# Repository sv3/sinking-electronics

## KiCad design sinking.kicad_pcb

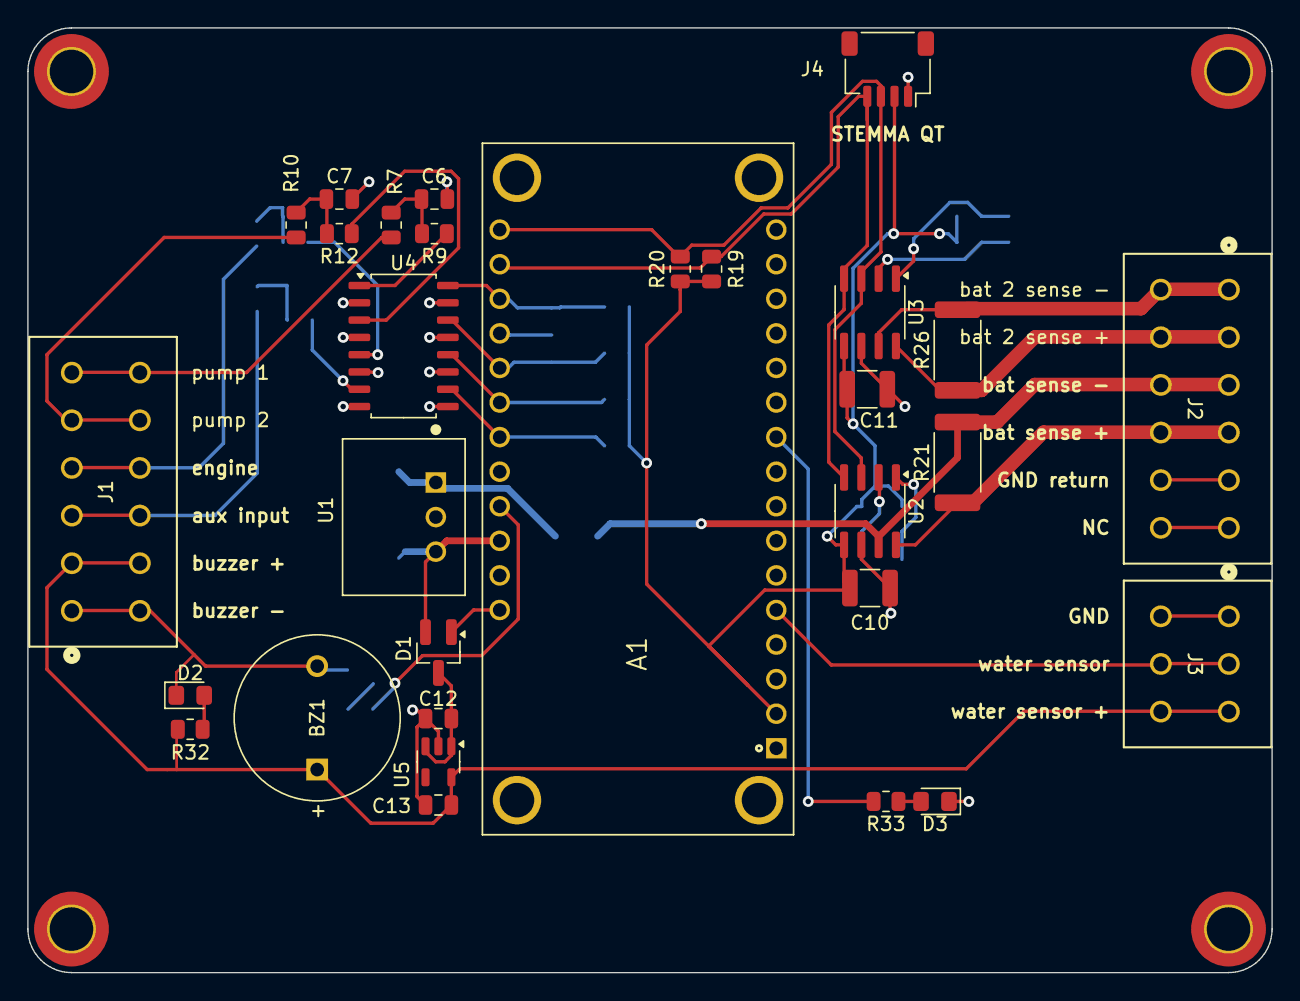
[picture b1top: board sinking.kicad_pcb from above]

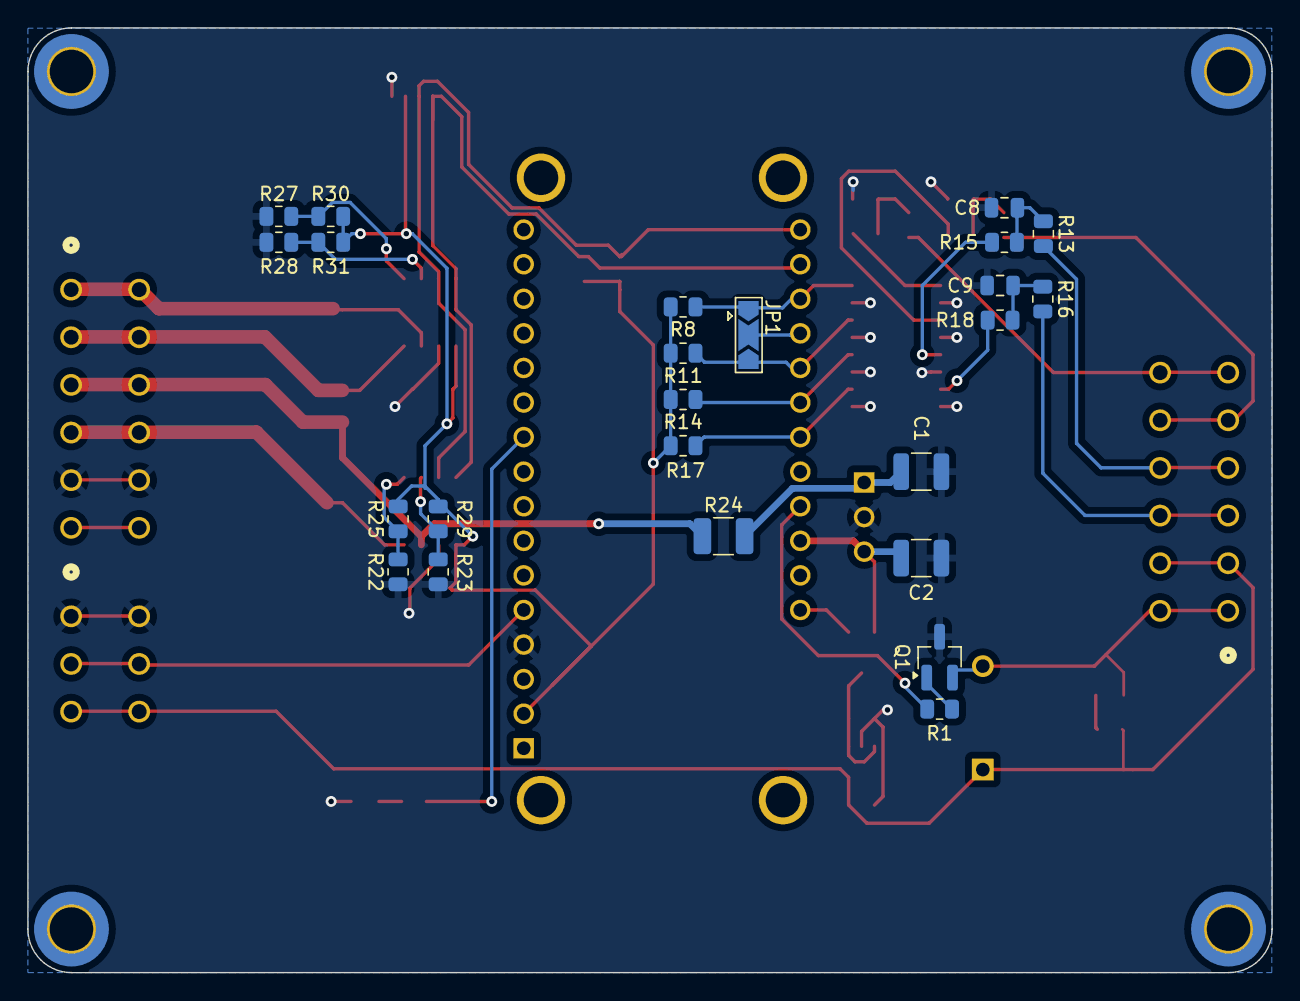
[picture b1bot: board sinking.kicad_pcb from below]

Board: 2 copper layers, 91.4 x 69.4 mm, 54 parts (24 on the bottom side), 42 nets.

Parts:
A1: Particle_Boron; Boron
BZ1: Buzzer; MagneticBuzzer_ProSignal_ABI-009-RC
C1: 10u; C_1210_3225Metric
C2: 22u; C_1210_3225Metric
C6, C7, C8, C9: 4.7u; C_0805_2012Metric
C10, C11: 0.1u; C_1210_3225Metric
C12, C13: 1u; C_0805_2012Metric
D1: PMEG2005; SOT-23_Handsoldering
D2: CTL0805FRD1T; LED_0805_2012Metric_Pad1.15x1.40mm_HandSolder
D3: LED; LED_0805_2012Metric_Pad1.15x1.40mm_HandSolder
J1, J2: 1861975; CONN_1861975
J3: 1861946; CONN_1861946
J4: SM04B-SRSS-TB; JST_SH_SM04B-SRSS-TB_1x04-1MP_P1.00mm_Horizontal
JP1: SolderJumper_3_Open; SolderJumper-3_P2.0mm_Open_TrianglePad1.0x1.5mm
Q1: Q_NPN_BCE; SOT-23_Handsoldering
R1: 1k; R_0805_2012Metric
R7, R9, R10, R12, R13, R15, R16, R18: 2.2k; R_0805_2012Metric
R8, R11, R14, R17: 4.7k; R_0805_2012Metric
R19, R20, R22, R23, R25, R27, R28, R29, R30, R31: 10k; R_0805_2012Metric
R21, R26: 0.1; R_2512_6332Metric
R24: 0; R_1210_3225Metric_Pad1.30x2.65mm_HandSolder
R32, R33: 330; R_0805_2012Metric
U1: V7805-1000; CONV_V7805-1000
U2, U3: INA219AxD; SOIC-8_3.9x4.9mm_P1.27mm
U4: TLP291-4; SOIC-16_4.55x10.3mm_P1.27mm
U5: TPS7A2033PDBVR; SOT-23-5

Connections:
+3V3: A1.3V3, C10.1, C11.1, J4.2, R8.2, R11.2, R14.2, R17.2, R19.2, R20.2, R25.2, R29.2, R30.2, R31.2, U2.5 (VS), U3.5 (VS)
/VUSB: A1.VUSB (VBUS), C2.1, D1.2, U1.3 (+VO)
/Vin: C1.1, R24.2, U1.1 (+VIN)
/input_filter1/out: A1.D4 (UART2_TX_SPI1_MISO_PWM1_P1.08_4), JP1.3 (B), R11.1, U4.14
/input_filter2/out: A1.D5 (UART2_RX_PWM1_P1.10_5), R14.1, U4.12
/input_filter3/out: A1.D6 (UART2_CTS_PWM1_P1.11_6), R17.1, U4.10
/input_filter/out: A1.D2 (SDA1_UART1_RTS_SPI1_SCK_PWM3_P1.01_2), JP1.1 (A), R8.1, U4.16
GND: A1.GND, C1.2, C2.2, C6.2, C7.2, C8.2, C9.2, C10.2, C11.2, C12.2, C13.2, D3.1 (K), J2.9, J2.10, J3.1, J3.2, J4.1, Q1.3 (E), R22.1, R23.1, R27.1, R28.1, U1.2 (GND), U2.6 (GND), U3.6 (GND), U4.2, U4.4, U4.6, U4.8, U4.9, U4.11, U4.13, U4.15, U5.2 (GND)
unnamed: A1.A5 (14_P0.31_PWM3_ADC5_SPI_SS), R33.2
unnamed: A1.LI+ (LiPo+), D1.1
unnamed: A1.D3 (SCL1_UART1_CTS_SPI1_MOSI_PWM3_P1.02_3), JP1.2 (C)
unnamed: A1.D8 (UART2_RTS_PWM1_P1.03_8), R1.1
unnamed: C6.1, R7.1, R9.2
unnamed: C7.1, R10.1, R12.2
unnamed: C8.1, R13.1, R15.2
unnamed: C9.1, R16.1, R18.2
unnamed: D2.2 (A), R32.2
unnamed: D3.2 (A), R33.1
unnamed: J2.11, J2.12
unnamed: Q1.1 (B), R1.2
unnamed: R9.1, U4.1
unnamed: R12.1, U4.3
unnamed: R15.1, U4.5
unnamed: R18.1, U4.7
unnamed: R23.2, R29.1, U2.2 (A0)
unnamed: R22.2, R25.1, U2.1 (A1)
unnamed: R28.2, R31.1, U3.2 (A0)
unnamed: R27.2, R30.1, U3.1 (A1)
unnamed: C12.1, D1.3, U5.1 (IN), U5.3 (EN)
SCL: A1.SCL (1_SCL_P0.27), J4.4, R19.1, U2.4 (SCL), U3.4 (SCL)
SDA: A1.SDA (0_SDA_P0.26), J4.3, R20.1, U2.3 (SDA), U3.3 (SDA)
aux_bat_sense_+: J2.3, J2.4, R26.1, U3.8 (IN+)
aux_bat_sense_-: J2.1, J2.2, R26.2, U3.7 (IN-)
aux_input: J1.5, J1.6, R16.2
bat_sense_+: J2.7, J2.8, R21.1, U2.8 (IN+)
bat_sense_-: J2.5, J2.6, R21.2, R24.1, U2.7 (IN-)
bilge_pump: J1.11, J1.12, R7.2
bilge_pump_2: J1.9, J1.10, R10.2
buzzer_+: BZ1.1 (+), C13.1, J1.3, J1.4, J3.5, J3.6, R32.1, U5.5 (OUT)
buzzer_-: BZ1.2 (-), D2.1 (K), J1.1, J1.2, Q1.2 (C)
engine_running: J1.7, J1.8, R13.2
water_sense_sig: A1.A0 (19_P0.03_PWM2_ADC0), J3.3, J3.4

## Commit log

2024-02-29 improve pump input filter. add simulation
2024-04-24 first layout
2024-04-26 add status led, etc.
